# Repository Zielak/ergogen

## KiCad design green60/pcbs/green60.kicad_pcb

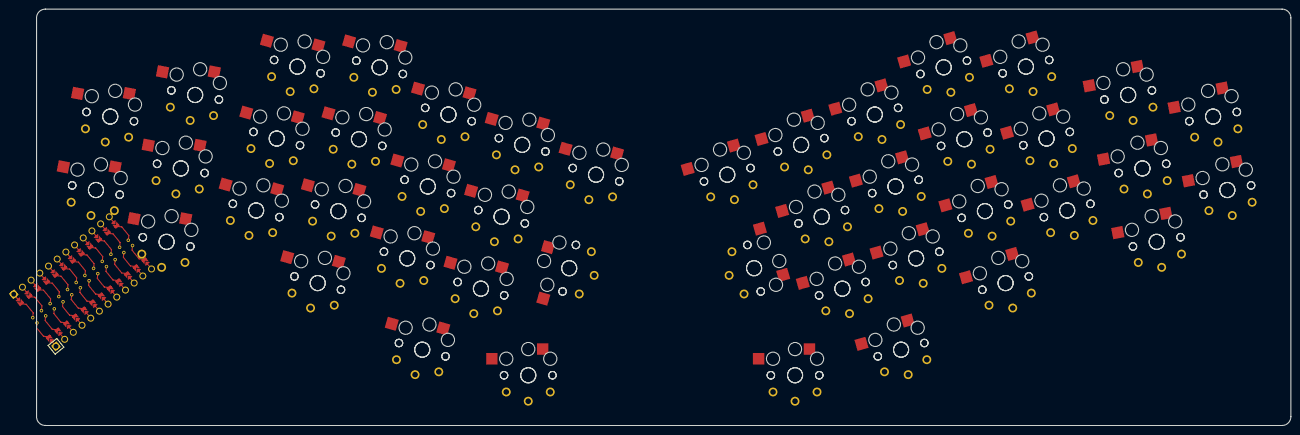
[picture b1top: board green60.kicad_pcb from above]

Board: 2 copper layers, 285.0 x 94.6 mm, 89 parts (0 on the bottom side), 10 nets, no tracks yet.

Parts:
MCU1: ProMicro
S1, S2, S3, S4, S5, S6, S7, S8, S9, S10, S11, S12, S13, S14, S15, S16, S17, S18, S19, S20, S21, S22, S23, S24, S25, S26, S27, S28, S29, S30, S31, S32, S33, S34, S35, S36, S37, S38, S39, S40, S41, S42, S43, S44, S45, S46, S47, S48, S49, S50, S51, S52, S53, S54, S55, S56, S57, S58, S59, S60, S61, S62, S63, S64, S65, S66, S67, S68, S69, S70, S71, S72, S73, S74, S75, S76, S77, S78, S79, S80, S81, S82, S83, S84, S85, S86, S87, S88: PG1350

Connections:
GND: MCU1.2, MCU1.21, MCU1.22, S1.2, S2.2, S3.2, S4.2, S5.2, S6.2, S7.2, S8.2, S9.2, S10.2, S11.2, S12.2, S13.2, S14.2, S15.2, S16.2, S17.2, S18.2, S19.2, S20.2, S21.2, S22.2, S23.2, S24.2, S25.2, S26.2, S27.2, S28.2, S29.2, S30.2, S31.2, S32.2, S33.2, S34.2, S35.2, S36.2, S37.2, S38.2, S39.2, S40.2, S41.2, S42.2, S43.2, S44.2, S45.2, S46.2, S47.2, S48.2, S49.2, S50.2, S51.2, S52.2, S53.2, S54.2, S55.2, S56.2, S57.2, S58.2, S59.2, S60.2, S61.2, S62.2, S63.2, S64.2, S65.2, S66.2, S67.2, S68.2, S69.2, S70.2, S71.2, S72.2, S73.2, S74.2, S75.2, S76.2, S77.2, S78.2, S79.2, S80.2, S81.2, S82.2, S83.2, S84.2, S85.2, S86.2, S87.2, S88.2
P0: MCU1.23, S1.1, S2.1, S3.1, S4.1, S45.1, S46.1, S47.1, S48.1
P1: MCU1.24, S5.1, S6.1, S7.1, S8.1, S9.1, S10.1, S49.1, S50.1, S51.1, S52.1, S53.1, S54.1
P2: MCU1.20, S11.1, S12.1, S13.1, S14.1, S15.1, S16.1, S55.1, S56.1, S57.1, S58.1, S59.1, S60.1
P3: MCU1.19, S17.1, S18.1, S19.1, S20.1, S21.1, S22.1, S23.1, S24.1, S61.1, S62.1, S63.1, S64.1, S65.1, S66.1, S67.1, S68.1
P4: MCU1.18, S25.1, S26.1, S27.1, S28.1, S29.1, S30.1, S69.1, S70.1, S71.1, S72.1, S73.1, S74.1
P5: MCU1.17, S31.1, S32.1, S33.1, S34.1, S35.1, S36.1, S75.1, S76.1, S77.1, S78.1, S79.1, S80.1
P6: MCU1.16, S37.1, S38.1, S39.1, S40.1, S81.1, S82.1, S83.1, S84.1
P7: MCU1.15, S41.1, S42.1, S85.1, S86.1
P8: MCU1.14, S43.1, S44.1, S87.1, S88.1

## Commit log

2022-08-02 feat: added diode for choc + green60 keeb
2022-08-12 feat: update kicad, chok diode reversible etc WIP
2022-08-22 gamma, more keys
2023-02-28 backup, some local experiments
